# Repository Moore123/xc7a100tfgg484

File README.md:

# xc7a100tfgg484
xc7a100t core board

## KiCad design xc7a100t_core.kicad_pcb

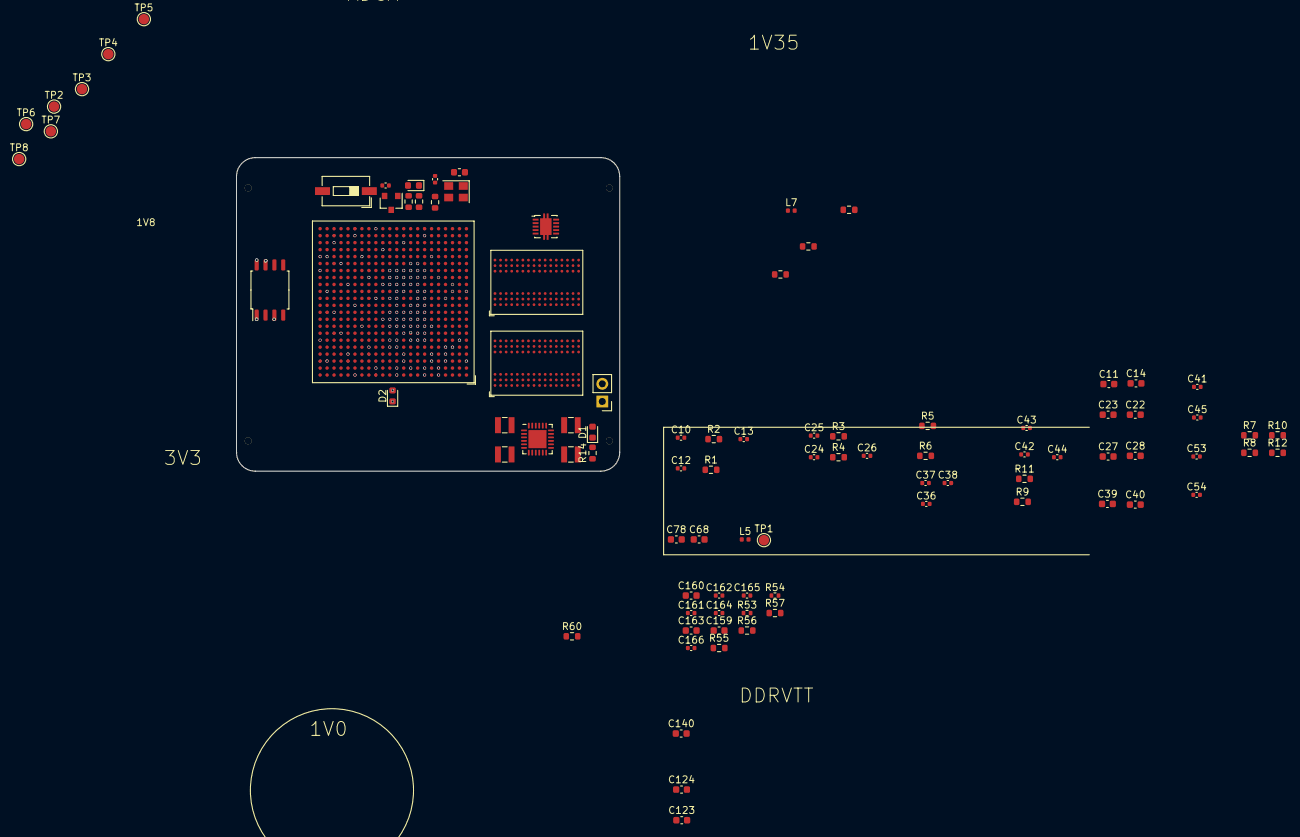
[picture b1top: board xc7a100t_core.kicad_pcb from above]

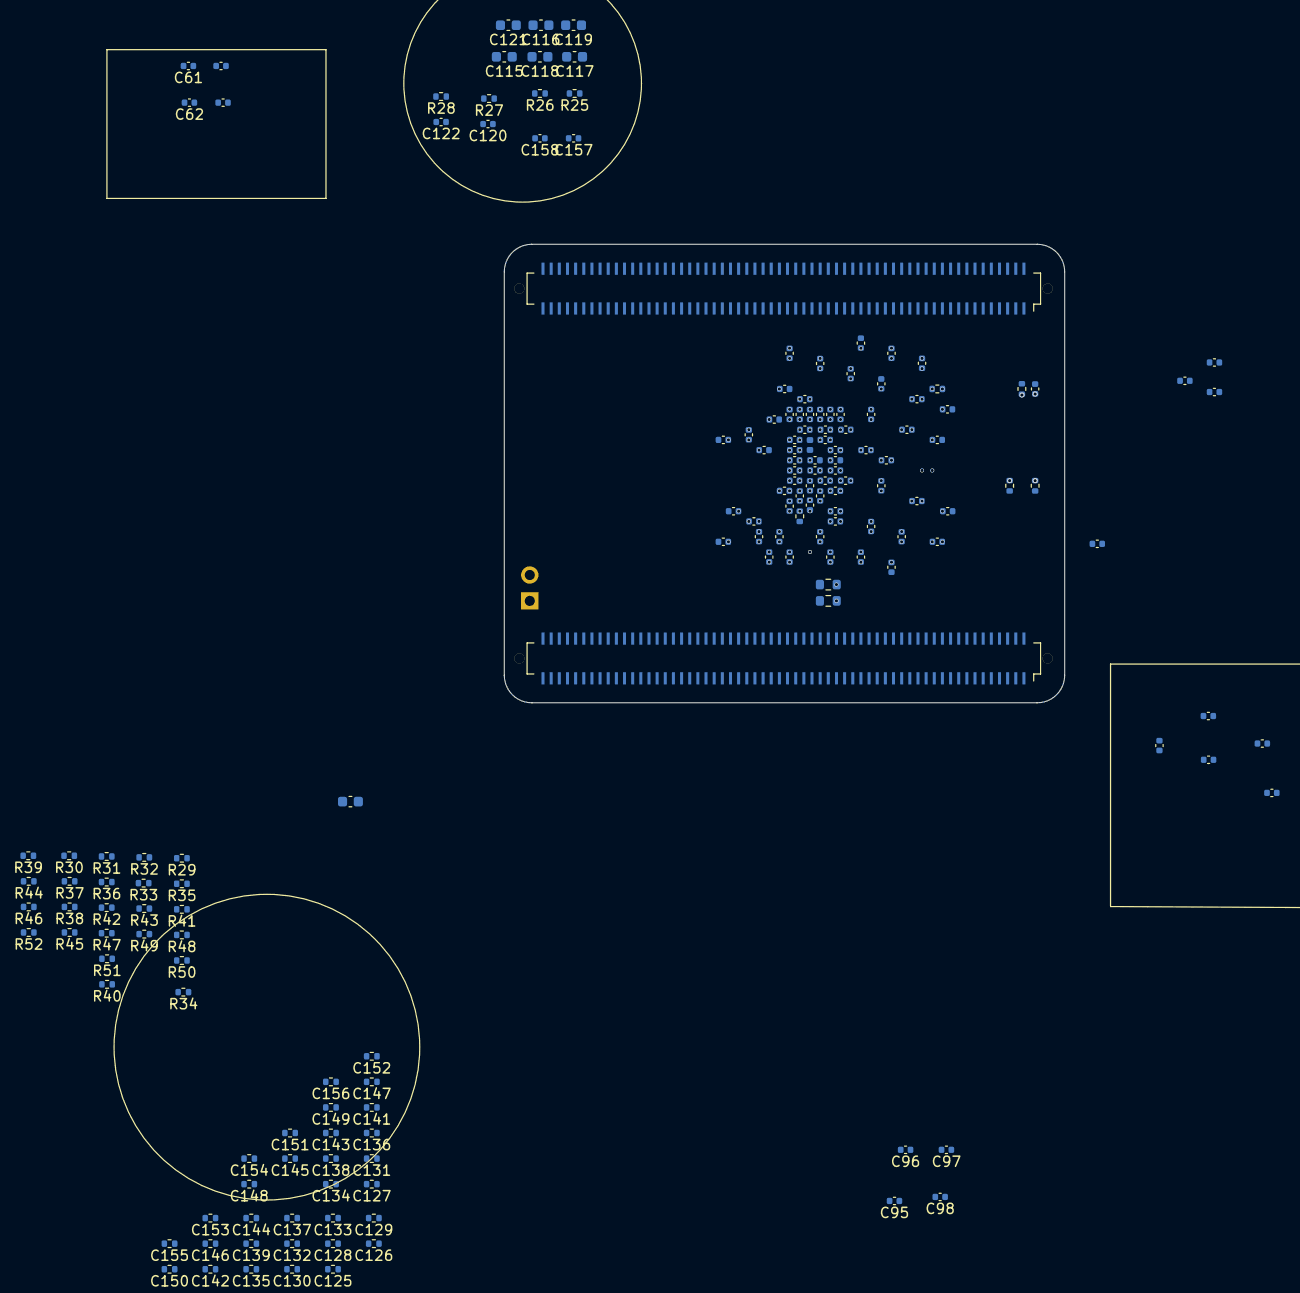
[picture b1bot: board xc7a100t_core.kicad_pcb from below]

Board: 6 copper layers, 55.0 x 45.0 mm, 258 parts (166 on the bottom side), 277 nets.

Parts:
C1, C4, C10, C15, C24, C29, C36, C42, C46, C69, C89, C90, C91, C92, C107: 22u; C_0402_1005Metric
C2, C5, C6, C16, C17, C30, C31, C47, C48, C55, C56, C61, C62, C70, C71, C72, C79, C83, C87, C93, C94, C95, C96, C97, C98: 4u7; C_0402_1005Metric
C3, C7, C8, C9, C12, C18, C19, C20, C21, C25, C32, C33, C34, C35, C37, C41, C43, C45, C49, C50, C51, C52, C53, C54, C57, C58, C59, C60, C63, C64, C65, C66, C73, C74, C75, C76, C77, C80, C81, C82, C84, C85, C86, C88, C99, C100, C101, C102, C103, C104, C105, C106, C108, C109, C110, C111, C112, C113, C114, C157, C158, C161, C164, C167: .1u; C_0402_1005Metric
C11, C22, C27, C39, C115, C116, C117, C118, C119, C121, C123, C140: 10u; C_0603_1608Metric
C13, C26, C38, C44: 220p; C_0402_1005Metric
C14, C23, C28, C40, C124: .1u; C_0603_1608Metric
C67, C68, C78: 22u; C_0603_1608Metric
C120, C122: .01u; C_0402_1005Metric
C125, C126, C127, C128, C129, C130, C131, C132, C133, C134, C135, C136, C137, C138, C139, C141, C142, C143, C144, C145, C146, C147, C148, C149, C150, C151, C152, C153, C154, C155, C156: .1u; R_0402_1005Metric
C159, C160, C163: 4u7; C_0603_1608Metric
C162, C165: 10n; C_0402_1005Metric
C166: 0.1u; C_0402_1005Metric
D1, D2, D3: LED; LED_0603_1608Metric
J1: Conn_01x02_Female; PinHeader_1x02_P2.54mm_Vertical
J2, J3: Conn_02x60_Odd_Even; Molex_SlimStack_55560-0801_2x60_P0.5mm_Vertical
L1, L2, L3, L4: 1.5uH; L_Wuerth_MAPI-2512
L5, L6, L7: .1uH; L_0402_1005Metric
L8: L_Small; L_0603_1608Metric
Q1: MMBT3904; SOT-23
R1, R2, R3, R4, R5, R6, R9, R11: R_Small; R_0603_1608Metric
R7, R8, R10, R12: 100K; R_0603_1608Metric
R13: 100; R_0402_1005Metric
R14, R16, R17: 4k7; R_0603_1608Metric
R15, R19, R58, R59, R60: 1k; R_0603_1608Metric
R18: 3k3; R_0603_1608Metric
R20, R21, R22, R24: 4k7; R_0402_1005Metric
R23: 33R; R_0603_1608Metric
R25: 100k; R_0402_1005Metric
R26, R27, R28: 10k; R_0402_1005Metric
R29, R30, R31, R32, R33, R34, R35, R36, R37, R38, R39, R40, R41, R42, R43, R44, R45, R46, R47, R48, R49, R50, R51, R52: 49R9; R_0402_1005Metric
R53, R54: 240; R_0402_1005Metric
R55, R56: 49R9; R_0603_1608Metric
R57: 4K7; R_0603_1608Metric
SW1: SW_Push; SW_DIP_SPSTx01_Slide_6.7x4.1mm_W6.73mm_P2.54mm_LowProfile_J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
TP1, TP2, TP3, TP4, TP5, TP6, TP7, TP8: TestPoint; TestPoint_Pad_D1.5mm
U1: XC7A100T-FGG484; BGA-484_23.0x23.0mm_Layout22x22_P1.0mm
U2: W25Q128JVS; SOIC-8_5.23x5.23mm_P1.27mm
U4, U5: NT5CB256M8IN; BGA-96_9.0x13.0mm_Layout2x3x16_P0.8mm
U6: TPS51200DRC; VSON-10-1EP_3x3mm_P0.5mm_EP1.65x2.4mm
U?1: EA3059QDR; QFN-24-1EP_4x4mm_P0.5mm_EP2.6x2.6mm
X1: ASE-50MHz; Oscillator_SMD_Abracon_ASE-4Pin_3.2x2.5mm

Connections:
+1V0: C10.1, C12.1, C13.1, C89.1, C90.1, C91.1, C92.1, C93.1, C94.1, C95.1, C96.1, C97.1, C98.1, C99.1, C100.1, C101.1, C102.1, C103.1, C104.1, C105.1, C106.1, C107.1, C108.1, C109.1, C110.1, L1.1, L5.1, R1.1, TP8.1, U1.H8, U1.H10, U1.J7, U1.J9, U1.J11, U1.K8, U1.L7, U1.L11, U1.M8, U1.N7, U1.N11, U1.P8, U1.P10, U1.R7, U1.R9, U1.T8, U1.T10
+1V8: C36.1, C37.1, C38.1, C69.1, C70.1, C71.1, C72.1, C73.1, C74.1, C75.1, C76.1, C77.1, L3.1, L6.1, R5.1, R8.1, R12.1, TP6.1, U1.E12, U1.H12, U1.K12, U1.M12, U1.P12, U1.R11
+1V35: C24.1, C25.1, C26.1, C55.1, C56.1, C57.1, C58.1, C59.1, C60.1, C61.1, C62.1, C63.1, C64.1, C65.1, C66.1, C116.1, C119.1, C123.1, C124.1, C125.1, C126.1, C127.1, C128.1, C129.1, C130.1, C131.1, C132.1, C133.1, C134.1, C135.1, C136.1, C137.1, C138.1, C139.1, C140.1, C141.1, C142.1, C143.1, C144.1, C145.1, C146.1, C147.1, C148.1, C149.1, C150.1, C151.1, C152.1, C153.1, C154.1, C155.1, C156.1, C166.1, L2.1, R3.1, R26.1, R60.1, TP7.1, U1.AA7, U1.AB4, U1.C1, U1.F2, U1.H6, U1.J3, U1.M4, U1.N1, U1.R5, U1.T2, U1.V6, U1.W3, U4.A1, U4.A8, U4.B2, U4.C1, U4.C9, U4.D2, U4.D9, U4.E9, U4.F1, U4.G7, U4.H2, U4.H9, U4.K2, U4.K8, U4.N1, U4.N9, U4.R1, U4.R9, U5.A1, U5.A8, U5.B2, U5.C1, U5.C9, U5.D2, U5.D9, U5.E9, U5.F1, U5.G7, U5.H2, U5.H9, U5.K2, U5.K8, U5.N1, U5.N9, U5.R1, U5.R9, U6.2
+3V3: C1.1, C2.1, C3.1, C4.1, C5.1, C6.1, C7.1, C8.1, C9.1, C15.1, C16.1, C17.1, C18.1, C19.1, C20.1, C21.1, C29.1, C30.1, C31.1, C32.1, C33.1, C34.1, C35.1, C42.1, C43.1, C44.1, C46.1, C47.1, C48.1, C49.1, C50.1, C51.1, C52.1, C111.1, C121.1, D1.2, D3.2, L4.1, L8.1, R9.1, R15.1, R16.1, R17.1, R19.1, R20.1, R21.1, R22.1, R25.2, TP4.1, U1.A17, U1.AA17, U1.AB14, U1.B14, U1.C21, U1.D18, U1.E15, U1.F12, U1.F22, U1.G19, U1.H16, U1.J13, U1.K20, U1.L17, U1.M14, U1.N21, U1.P18, U1.R15, U1.T12, U1.T22, U1.U8, U1.U19, U1.V16, U1.W13, U1.Y10, U1.Y20, U2.8, U6.7, U6.10
/Jtag/FPGA_DONE: D2.2, R19.2, U1.G11
/Power/VCCADC: C87.1, C88.1, L6.2, U1.K10
B13_IO0: J2.5, U1.Y17
B13_L1N: J2.9, U1.AA16
B13_L1P: J2.7, U1.Y16
B13_L2N: J2.13, U1.AB17
B13_L2P: J2.11, U1.AB16
B13_L3N: J2.17, U1.AB13
B13_L3P: J2.15, U1.AA13
B13_L4N: J2.21, U1.AB15
B13_L4P: J2.19, U1.AA15
B13_L5N: J2.25, U1.AA14
B13_L5P: J2.23, U1.Y13
B13_L6N: J2.29, U1.Y14
B13_L6P: J2.27, U1.W14
B13_L7N: J2.33, U1.AB12
B13_L7P: J2.31, U1.AB11
B13_L8N: J2.37, U1.AB10
B13_L8P: J2.35, U1.AA9
B13_L9N: J2.41, U1.AA11
B13_L9P: J2.39, U1.AA10
B13_L10N: J2.45, U1.W10
B13_L10P: J2.43, U1.V10
B13_L11N: J2.49, U1.Y12
B13_L11P: J2.47, U1.Y11
B13_L12N: J2.53, U1.W12
B13_L12P: J2.51, U1.W11
B13_L13N: J2.57, U1.V14
B13_L13P: J2.55, U1.V13
B13_L14N: J2.61, U1.V15
B13_L14P: J2.59, U1.U15
B13_L15N: J2.65, U1.T15
B13_L15P: J2.63, U1.T14
B13_L16N: J2.69, U1.W16
B13_L16P: J2.67, U1.W15
B13_L17N: J2.73, U1.U16
B13_L17P: J2.71, U1.T16
B14_IO25: J2.90, U1.N15
B14_L4N: J2.8, U1.U21
B14_L4P: J2.6, U1.T21
B14_L5N: J2.12, U1.R19
B14_L5P: J2.10, U1.P19
B14_L6N: J2.16, U1.T20
B14_L6P: J2.14, U1.T19
B14_L7N: J2.20, U1.W22
B14_L7P: J2.18, U1.W21
B14_L8N: J2.24, U1.AA21
B14_L8P: J2.22, U1.AA20
B14_L9N: J2.28, U1.Y22
B14_L9P: J2.26, U1.Y21
B14_L10N: J2.32, U1.AB22
B14_L10P: J2.30, U1.AB21
B14_L11N: J2.36, U1.V20
B14_L11P: J2.34, U1.U20
B14_L12N: J2.40, U1.W20
B14_L12P: J2.38, U1.W19
B14_L13N: J2.44, U1.Y19
B14_L13P: J2.42, U1.Y18
B14_L14N: J2.48, U1.V19
B14_L14P: J2.46, U1.V18
B14_L15N: J2.52, U1.AB20
B14_L15P: J2.50, U1.AA19
B14_L16N: J2.56, U1.W17
B14_L16P: J2.54, U1.V17
B14_L17N: J2.60, U1.AB18
B14_L17P: J2.58, U1.AA18
B14_L18N: J2.64, U1.U18
B14_L18P: J2.62, U1.U17
B14_L19N: J2.68, U1.R14
B14_L19P: J2.66, U1.P14
B14_L20N: J2.72, U1.T18
B14_L20P: J2.70, U1.R18
B14_L21N: J2.76, U1.P17
B14_L21P: J2.74, U1.N17
B14_L22N: J2.80, U1.R16
B14_L22P: J2.78, U1.P15
B14_L23N: J2.84, U1.N14
B14_L23P: J2.82, U1.N13
B14_L24N: J2.88, U1.R17
B14_L24P: J2.86, U1.P16
B15_IO0: J3.6, U1.J16
B15_IO25: J3.104, U1.M17
B15_L1N: J3.10, U1.G13
B15_L1P: J3.8, U1.H13
B15_L2N: J3.14, U1.G16
B15_L2P: J3.12, U1.G15
B15_L3N: J3.18, U1.H14
B15_L3P: J3.16, U1.J14
B15_L4N: J3.22, U1.G18
B15_L4P: J3.20, U1.G17
B15_L5N: J3.26, U1.H15
B15_L5P: J3.24, U1.J15
B15_L6N: J3.30, U1.H18
B15_L6P: J3.28, U1.H17
B15_L7N: J3.34, U1.H22
B15_L7P: J3.32, U1.J22
B15_L8N: J3.38, U1.G20
B15_L8P: J3.36, U1.H20
B15_L9N: J3.42, U1.K22
B15_L9P: J3.40, U1.K21
B15_L10N: J3.46, U1.L21
B15_L10P: J3.44, U1.M21
B15_L11N: J3.50, U1.J21
B15_L11P: J3.48, U1.J20
B15_L12N: J3.54, U1.H19
B15_L12P: J3.52, U1.J19
B15_L13N: J3.58, U1.K19
B15_L13P: J3.56, U1.K18
B15_L14N: J3.62, U1.L20
B15_L14P: J3.60, U1.L19
B15_L15N: J3.66, U1.M22
B15_L15P: J3.64, U1.N22
B15_L16N: J3.70, U1.L18
B15_L16P: J3.68, U1.M18
B15_L17N: J3.74, U1.N19
B15_L17P: J3.72, U1.N18
B15_L18N: J3.78, U1.M20
B15_L18P: J3.76, U1.N20
B15_L19N: J3.82, U1.K14
B15_L19P: J3.80, U1.K13
B15_L20N: J3.86, U1.L13
B15_L20P: J3.84, U1.M13
B15_L21N: J3.90, U1.J17
B15_L21P: J3.88, U1.K17
B15_L22N: J3.94, U1.L15
B15_L22P: J3.92, U1.L14
B15_L23N: J3.98, U1.K16
B15_L23P: J3.96, U1.L16
B15_L24N: J3.102, U1.M16
B15_L24P: J3.100, U1.M15
B16_IO0: J3.103, U1.F15
B16_IO25: J3.5, U1.F21
B16_L1N: J3.99, U1.F14
B16_L1P: J3.101, U1.F13
B16_L2N: J3.95, U1.E17
B16_L2P: J3.97, U1.F16
B16_L3N: J3.91, U1.C15
B16_L3P: J3.93, U1.C14
B16_L4N: J3.87, U1.E14
B16_L4P: J3.89, U1.E13
B16_L5N: J3.83, U1.D16
B16_L5P: J3.85, U1.E16
B16_L6N: J3.79, U1.D15
B16_L6P: J3.81, U1.D14
B16_L7N: J3.75, U1.B16
B16_L7P: J3.77, U1.B15
B16_L8N: J3.71, U1.B13
B16_L8P: J3.73, U1.C13
B16_L9N: J3.67, U1.A16
B16_L9P: J3.69, U1.A15
B16_L10N: J3.63, U1.A14
B16_L10P: J3.65, U1.A13
B16_L11N: J3.59, U1.B18
B16_L11P: J3.61, U1.B17
B16_L12N: J3.55, U1.C17
B16_L12P: J3.57, U1.D17
B16_L13N: J3.51, U1.C19
B16_L13P: J3.53, U1.C18
B16_L14N: J3.47, U1.D19
B16_L14P: J3.49, U1.E19
B16_L15N: J3.43, U1.E18
B16_L15P: J3.45, U1.F18
B16_L16N: J3.39, U1.A20
B16_L16P: J3.41, U1.B20
B16_L17N: J3.35, U1.A19
B16_L17P: J3.37, U1.A18
B16_L18N: J3.31, U1.F20
B16_L18P: J3.33, U1.F19
B16_L19N: J3.27, U1.C20
B16_L19P: J3.29, U1.D20
B16_L20N: J3.23, U1.B22
B16_L20P: J3.25, U1.C22
B16_L21N: J3.21, U1.A21
B16_L21P: J3.19, U1.B21
B16_L22N: J3.17, U1.D22
B16_L22P: J3.15, U1.E22
B16_L23N: J3.13, U1.D21
B16_L23P: J3.11, U1.E21
B16_L24N: J3.9, U1.G22
B16_L24P: J3.7, U1.G21
DDRVTT: C115.1, C117.1, C118.1, C159.1, C160.1, C161.1, C162.1, C163.1, C164.1, C165.1, R29.2, R30.2, R31.2, R32.2, R33.2, R34.2, R35.2, R36.2, R37.2, R38.2, R39.2, R40.2, R41.2, R42.2, R43.2, R44.2, R45.2, R46.2, R47.2, R48.2, R49.2, R50.2, R51.2, R52.2, U6.3, U6.5
DDR_A0: R29.1, U1.AA4, U4.N3, U5.N3
DDR_A1: R30.1, U1.AB2, U4.P7, U5.P7
DDR_A2: R31.1, U1.AA5, U4.P3, U5.P3
DDR_A3: R32.1, U1.AB5, U4.N2, U5.N2
DDR_A4: R33.1, U1.AB1, U4.P8, U5.P8
DDR_A5: R34.1, U1.U3, U4.P2, U5.P2
DDR_A6: R35.1, U1.W1, U4.R8, U5.R8
DDR_A7: R36.1, U1.T1, U4.R2, U5.R2
DDR_A8: R37.1, U1.V2, U4.T8, U5.T8
DDR_A9: R38.1, U1.U2, U4.R3, U5.R3
DDR_A10: R39.1, U1.Y1, U4.L7, U5.L7
DDR_A11: R40.1, U1.W2, U4.R7, U5.R7
DDR_A12: R41.1, U1.Y2, U4.N7, U5.N7
DDR_A13: R42.1, U1.U1, U4.T3, U5.T3
DDR_A14: R43.1, U1.V3, U4.T7, U5.T7
DDR_BA0: R44.1, U1.AA3, U4.M2, U5.M2
DDR_BA1: R45.1, U1.Y3, U4.N8, U5.N8
DDR_BA2: R46.1, U1.Y4, U4.M3, U5.M3
DDR_CAS: R49.1, U1.W4, U4.K3, U5.K3
DDR_CKE0: R52.1, U1.T5, U4.K9, U5.K9
DDR_CLK0_N: R56.2, U1.R2, U4.K7, U5.K7
DDR_CLK0_P: R55.2, U1.R3, U4.J7, U5.J7
DDR_D0: U1.C2, U4.E3, U5.E3
DDR_D1: U1.G1, U4.F7, U5.F7
DDR_D2: U1.A1, U4.F2, U5.F2
DDR_D3: U1.F3, U4.F8, U5.F8
DDR_D4: U1.B2, U4.H3, U5.H3
DDR_D5: U1.F1, U4.H8, U5.H8
DDR_D6: U1.B1, U4.G2, U5.G2
DDR_D7: U1.E2, U4.H7, U5.H7
DDR_D8: U1.H3, U4.D7, U5.D7
DDR_D9: U1.G3, U4.C3, U5.C3
DDR_D10: U1.H2, U4.C8, U5.C8
DDR_D11: U1.H5, U4.C2, U5.C2
DDR_D12: U1.J1, U4.A7, U5.A7
DDR_D13: U1.J5, U4.A2, U5.A2
DDR_D14: U1.K1, U4.B8, U5.B8
DDR_D15: U1.H4, U4.A3, U5.A3
DDR_DM0: U1.D2, U4.E7, U5.E7
DDR_DM1: U1.G2, U4.D3, U5.D3
DDR_DQS2_N: U1.L1, U5.G3
DDR_DQS2_P: U1.M1, U5.F3
DDR_DQS3_P: U1.P5, U5.C7
DDR_ODT: R51.1, U1.U5, U4.K1, U5.K1
DDR_RAS: R48.1, U1.V4, U4.J3, U5.J3
DDR_RESET: R57.1, U1.W6, U4.T2, U5.T2
DDR_S0: R47.1, U1.AB3, U4.L2, U5.L2
DDR_WE: R50.1, U1.AA1, U4.L3, U5.L3
GNDA: C87.2, C88.2, L7.1, TP5.1, U1.K9, U1.L9, U1.M10
GNDREF: C1.2, C2.2, C3.2, C4.2, C5.2, C6.2, C7.2, C8.2, C9.2, C10.2, C11.2, C12.2, C14.2, C15.2, C16.2, C17.2, C18.2, C19.2, C20.2, C21.2, C22.2, C23.2, C24.2, C25.2, C27.2, C28.2, C29.2, C30.2, C31.2, C32.2, C33.2, C34.2, C35.2, C36.2, C37.2, C39.2, C40.2, C41.2, C42.2, C43.2, C45.2, C46.2, C47.2, C48.2, C49.2, C50.2, C51.2, C52.2, C53.1, C54.1, C55.2, C56.2, C57.2, C58.2, C59.2, C60.2, C61.2, C62.2, C63.2, C64.2, C65.2, C66.2, C67.1, C68.2, C69.2, C70.2, C71.2, C72.2, C73.2, C74.2, C75.2, C76.2, C77.2, C78.2, C79.2, C80.2, C81.2, C82.2, C83.2, C84.2, C85.2, C86.2, C89.2, C90.2, C91.2, C92.2, C93.2, C94.2, C95.2, C96.2, C97.2, C98.2, C99.2, C100.2, C101.2, C102.2, C103.2, C104.2, C105.2, C106.2, C107.2, C108.2, C109.2, C110.2, C111.2, C112.2, C113.2, C114.2, C115.2, C116.2, C117.2, C118.2, C119.2, C120.2, C121.2, C122.2, C123.2, C124.2, C125.2, C126.2, C127.2, C128.2, C129.2, C130.2, C131.2, C132.2, C133.2, C134.2, C135.2, C136.2, C137.2, C138.2, C139.2, C140.2, C141.2, C142.2, C143.2, C144.2, C145.2, C146.2, C147.2, C148.2, C149.2, C150.2, C151.2, C152.2, C153.2, C154.2, C155.2, C156.2, C157.2, C158.2, C159.2, C160.2, C161.2, C162.2, C163.2, C164.2, C165.2, C167.2, J1.2, L7.2, Q1.2, R2.2, R4.2, R6.2, R11.2, R14.1, R18.2, R24.1, R27.2, R28.2, R53.2, R54.2, R57.2, SW1.2, TP2.1, U1.A2, U1.A3, U1.A5, U1.A7, U1.A9, U1.A11, U1.A12, U1.A22, U1.AA2, U1.AA12, U1.AA22, U1.AB9, U1.AB19, U1.B3, U1.B12, U1.B19, U1.C3, U1.C6, U1.C10, U1.C12, U1.C16, U1.D3, U1.D4, U1.D8, U1.D12, U1.D13, U1.E4, U1.E5, U1.E7, U1.E9, U1.E11, U1.E20, U1.F5, U1.F11, U1.F17, U1.G5, U1.G6, U1.G7, U1.G8, U1.G9, U1.G10, U1.G12, U1.G14, U1.H1, U1.H7, U1.H9, U1.H11, U1.H21, U1.J8, U1.J10, U1.J12, U1.J18, U1.K5, U1.K7, U1.K11, U1.K15, U1.L2, U1.L8, U1.L22, U1.M7, U1.M11, U1.M19, U1.N6, U1.N8, U1.N9, U1.N10, U1.N16, U1.P3, U1.P7, U1.P9, U1.P11, U1.P13, U1.R8, U1.R10, U1.R12, U1.R20, U1.T7, U1.T9, U1.T11, U1.T17, U1.U4, U1.U9, U1.U10, U1.U14, U1.V1, U1.V11, U1.V21, U1.W8, U1.W18, U1.Y5, U1.Y15, U2.4, U4.A9, U4.B1, U4.B3, U4.B9, U4.D1, U4.D8, U4.E1, U4.E2, U4.E8, U4.F9, U4.G1, U4.G8, U4.G9, U4.J2, U4.J8, U4.M1, U4.M9, U4.P1, U4.P9, U4.T1, U4.T9, U5.A9, U5.B1, U5.B3, U5.B9, U5.D1, U5.D8, U5.E1, U5.E2, U5.E8, U5.F9, U5.G1, U5.G8, U5.G9, U5.J2, U5.J8, U5.M1, U5.M9, U5.P1, U5.P9, U5.T1, U5.T9, U6.4, U6.8, U6.11, U?1.1, U?1.4, U?1.6, U?1.13, U?1.18, U?1.25, X1.2
LED1: R59.2, U1.W5
MGTAVCC: C67.2, C83.1, C84.1, C85.1, C86.1, L5.2, TP1.1, U1.D6, U1.D10, U1.E8, U1.F7, U1.F9
MGTAVTT: C79.1, C80.1, C81.1, C82.1, R13.1, U1.B5, U1.B7, U1.B9, U1.B11, U1.C4, U1.C8
unnamed: C13.2, R1.2, R2.1, U?1.14
unnamed: C26.2, R3.2, R4.1, U?1.5
unnamed: C38.2, R5.2, R6.1, U?1.2
unnamed: C41.1, R7.2, U?1.10
unnamed: C44.2, R9.2, R11.1, U?1.17
unnamed: C45.1, R8.2, U?1.9
unnamed: C53.2, R10.2, U?1.22
unnamed: C54.2, R12.2, U?1.21
unnamed: C112.1, L8.2, X1.1, X1.4
unnamed: C120.1, R26.2, R27.1, U6.1
unnamed: C166.2, R55.1, R56.1
unnamed: D1.1, R14.2
unnamed: D2.1, R18.1
unnamed: D3.1, R58.1
unnamed: L1.2, U?1.12
unnamed: L2.2, U?1.7
unnamed: L3.2, U?1.24
unnamed: L4.2, U?1.19
unnamed: Q1.1, R59.1
unnamed: Q1.3, R58.2
unnamed: R13.2, U1.F8
unnamed: R15.2, U1.U11
unnamed: R16.2, U1.U12
unnamed: R17.2, U1.N12
unnamed: R23.2, X1.3
unnamed: R24.2, U1.V22
unnamed: R25.1, U6.9
unnamed: R53.1, U5.L8
unnamed: R54.1, U4.L8
QSPI_CLK: U1.L12, U2.6
QSPI_CS: R20.2, U2.1
QSPI_DQ0: U1.P22, U2.5
QSPI_DQ1: U1.R22, U2.2
QSPI_DQ2: R21.2, U1.P21, U2.3
QSPI_DQ3: R22.2, U1.R21, U2.7
RESET_N: C167.1, R60.2, SW1.1, U1.U7
SYS_CLK: R23.1, U1.R4
VCCIN: C11.1, C14.1, C22.1, C23.1, C27.1, C28.1, C39.1, C40.1, C68.1, C78.1, J1.1, R7.1, R10.1, TP3.1, U?1.8, U?1.11, U?1.20, U?1.23
VTTREF: C113.1, C114.1, C122.1, C157.1, C158.1, R28.1, U1.E3, U1.N3, U4.H1, U4.M8, U5.H1, U5.M8, U6.6

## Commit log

2023-12-12 initial upload, NOT DONE YET.
    Just beginning for now
